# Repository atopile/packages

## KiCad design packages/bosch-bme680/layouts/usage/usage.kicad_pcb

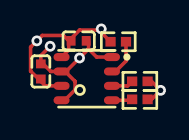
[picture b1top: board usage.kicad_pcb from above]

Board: 2 copper layers, 6 parts (0 on the bottom side), 5 nets.

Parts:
C1, C2: 0F; C0402
R1, R2, R3: 10000Ω; R0402
U1: LGA-8_L3.0-W3.0-P0.80-TR

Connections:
CSB: R1.2, U1.2
SCL: R2.2, U1.4
SDA: R3.2, U1.3
hv: C1.1, C2.1, R1.1, R2.1, R3.1, U1.6, U1.8
lv: C1.2, C2.2, U1.1, U1.5, U1.7

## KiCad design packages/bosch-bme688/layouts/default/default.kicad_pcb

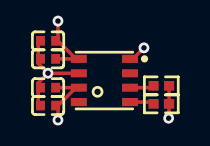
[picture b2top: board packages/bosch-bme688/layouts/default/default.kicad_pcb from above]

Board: 2 copper layers, 7 parts (0 on the bottom side), 4 nets.

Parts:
C1, C2, C3, C4: 0F; C0402
R1, R2: 4700Ω; R0402
U1: LGA-8_L3.0-W3.0-P0.80_BME688

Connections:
MOSI: R2.2, U1.3
SCL: R1.2, U1.4
hv: C1.1, C2.1, C3.1, C4.1, R1.1, R2.1, U1.6, U1.8
lv: C1.2, C2.2, C3.2, C4.2, U1.1, U1.5, U1.7

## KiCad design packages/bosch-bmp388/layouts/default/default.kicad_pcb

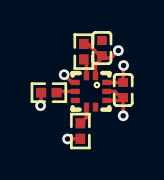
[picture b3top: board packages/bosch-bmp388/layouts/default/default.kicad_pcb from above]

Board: 2 copper layers, 6 parts (0 on the bottom side), 6 nets.

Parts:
C1, C2: 0F; C0402
R1, R2, R3: 10000Ω; R0402
U1: SENSORM-SMD_BMP388

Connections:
CSB: R1.2, U1.6
MOSI: R3.2, U1.4
SCL: R2.2, U1.2
decoupling_caps[0]-power-hv: C1.1, U1.10
hv: C2.1, R1.1, R2.1, R3.1, U1.1
lv: C1.2, C2.2, U1.3, U1.5, U1.8, U1.9
